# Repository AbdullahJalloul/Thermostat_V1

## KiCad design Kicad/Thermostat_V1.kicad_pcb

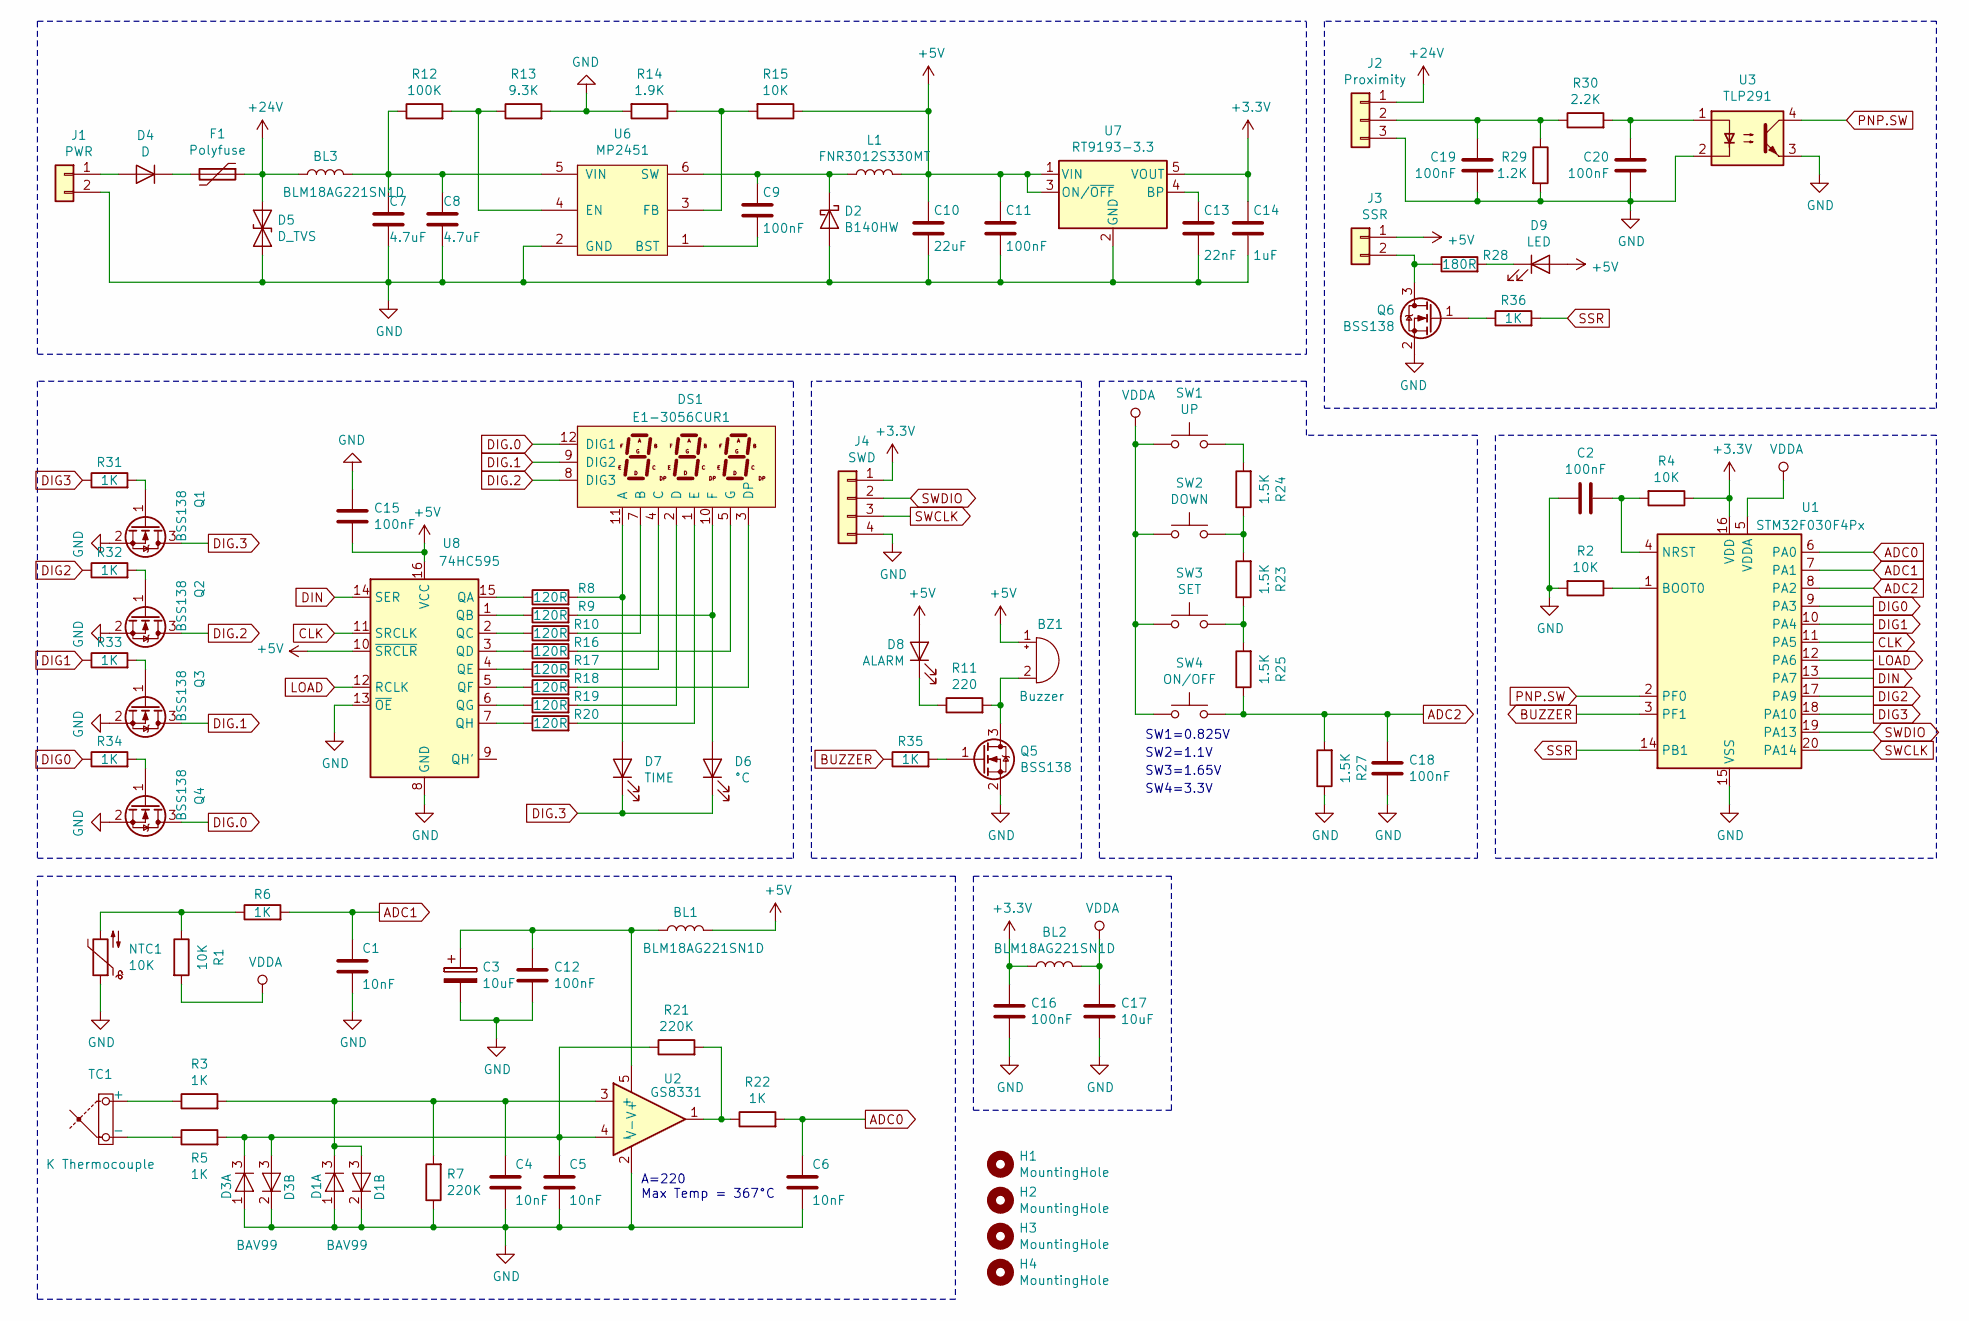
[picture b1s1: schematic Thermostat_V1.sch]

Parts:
BL1, BL2: BLM18AG221SN1D; L_0805
BL3: BLM18AG221SN1D; L_1206
BZ1: Buzzer; Buzzer_12x9.5RM7.6
C1, C4, C5, C6: 10nF; C_0805
C2, C9, C11, C12, C15, C16, C18, C19, C20: 100nF; C_0805
C3: 10uF; CP_Tantalum_Case-A_EIA-3216-18_Reflow
C7, C8: 4.7uF; C_1206
C10: 22uF; C_1206
C13: 22nF; C_0805
C14: 1uF; C_0805
C17: 10uF; C_0805
D1, D3: BAV99; SOT-23
D2: B140HW; D_SOD-123F
D4: D; D_SMA
D5: D_TVS; D_SMA
D6: °C; LED_D5.0mm
D7: TIME; LED_D5.0mm
D8: ALARM; LED_D5.0mm
D9: LED; LED_0805
DS1: E1-3056CUR1; E1-3056-CUR-1-CT
F1: Polyfuse; Fuse_1206_3216Metric
H1, H2, H3, H4: MountingHole; MountingHole_2.5mm
J1: PWR; TerminalBlock_bornier-2_P5.08mm
J2: Proximity; TerminalBlock_bornier-3_P5.08mm
J3: SSR; TerminalBlock_bornier-2_P5.08mm
J4: SWD; Pin_Header_Straight_1x04_Pitch2.54mm
L1: FNR3012S330MT; L_Taiyo-Yuden_MD-3030
NTC1: 10K; R_0805
Q1, Q2, Q3, Q4, Q5, Q6: BSS138; SOT-23
R1, R2, R4, R15: 10K; R_0805
R3, R5, R6, R22, R31, R32, R33, R34, R35, R36: 1K; R_0805
R7, R21: 220K; R_0805
R8, R9, R10, R16, R17, R18, R19, R20: 120R; R_0805
R11: 220; R_0805
R12: 100K; R_0805
R13: 9.3K; R_0805
R14: 1.9K; R_0805
R23, R24, R25, R27: 1.5K; R_0805
R28: 180R; R_0805
R29: 1.2K; R_2512
R30: 2.2K; R_0805
SW1: UP; SW_SPST_PTS645
SW2: DOWN; SW_SPST_PTS645
SW3: SET; SW_SPST_PTS645
SW4: ON/OFF; SW_SPST_PTS645
TC1: K Thermocouple; TerminalBlock_bornier-2_P5.08mm
U1: STM32F030F4Px; TSSOP-20_4.4x6.5mm_Pitch0.65mm
U2: GS8331; SOT-23-5
U3: TLP291; SO-4_4.4x2.3mm_Pitch1.27mm
U6: MP2451; SOT-23-6
U7: RT9193-3.3; SOT-23-5
U8: 74HC595; SOIC-16_3.9x9.9mm_Pitch1.27mm

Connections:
+3V3: BL2.1, C14.2, C16.2, J4.1, R4.1, U1.16 (VDD), U7.5 (VOUT)
+5V: BL1.2, BZ1.1 (-), C10.2, C11.2, C15.1, D8.2 (A), D9.2 (A), J3.1, L1.2, R15.1, U7.1 (VIN), U7.3 (ON/~OFF~), U8.10 (~SRCLR), U8.16 (VCC)
+24V: BL3.1, D5.1 (A1), F1.1, J2.1
ADC0: C6.2, R22.2, U1.6 (PA0)
ADC1: C1.2, R6.2, U1.7 (PA1)
ADC2: C18.2, R25.1, R27.2, SW4.2, U1.8 (PA2)
BUZZER: R35.1, U1.3 (PF1)
CLK: U1.11 (PA5), U8.11 (SRCLK)
DIG0: R34.1, U1.9 (PA3)
DIG1: R33.1, U1.10 (PA4)
DIG2: R32.1, U1.17 (PA9)
DIG3: R31.1, U1.18 (PA10)
DIG.0: DS1.12 (DIG1), Q4.3 (D)
DIG.1: DS1.9 (DIG2), Q3.3 (D)
DIG.2: DS1.8 (DIG3), Q2.3 (D)
DIG.3: D6.1 (K), D7.1 (K), Q1.3 (D)
DIN: U1.13 (PA7), U8.14 (SER)
GND: C1.1, C2.1, C3.2, C4.1, C5.1, C6.1, C7.1, C8.1, C10.1, C11.1, C12.1, C13.1, C14.1, C15.2, C16.1, C17.1, C18.1, C19.1, C20.1, D1.1 (A), D1.2 (K), D2.2 (A), D3.1 (A), D3.2 (K), D5.2 (A2), J1.2, J2.3, J4.4, NTC1.1, Q1.2 (S), Q2.2 (S), Q3.2 (S), Q4.2 (S), Q5.2 (S), Q6.2 (S), R2.2, R7.1, R13.2, R14.2, R27.1, R29.2, U1.15 (VSS), U2.2 (V-), U3.2, U3.3, U6.2 (GND), U7.2 (GND), U8.8 (GND), U8.13 (~OE)
LOAD: U1.12 (PA6), U8.12 (RCLK)
unnamed: BL1.1, C3.1, C12.2, U2.5 (V+)
unnamed: BL3.2, C7.2, C8.2, R12.1, U6.5 (VIN)
unnamed: BZ1.2 (+), Q5.3 (D), R11.2
unnamed: C2.2, R4.2, U1.4 (NRST)
unnamed: C4.2, D1.3 (K), R3.2, R7.2, U2.3 (+)
unnamed: C5.2, D3.3 (K), R5.2, R21.1, U2.4 (-)
unnamed: C9.1, U6.1 (BST)
unnamed: C9.2, D2.1 (K), L1.1, U6.6 (SW)
unnamed: C13.2, U7.4 (BP)
unnamed: C19.2, J2.2, R29.1, R30.1
unnamed: C20.2, R30.2, U3.1
unnamed: D4.1 (K), F1.2
unnamed: D4.2 (A), J1.1
unnamed: D6.2 (A), DS1.10 (F), R9.2
unnamed: D7.2 (A), DS1.11 (A), R8.2
unnamed: D8.1 (K), R11.1
unnamed: D9.1 (K), R28.2
unnamed: DS1.1 (E), R20.2
unnamed: DS1.2 (D), R19.2
unnamed: DS1.3 (DP), R18.2
unnamed: DS1.4 (C), R17.2
unnamed: DS1.5 (G), R16.2
unnamed: DS1.7 (B), R10.2
unnamed: J3.2, Q6.3 (D), R28.1
unnamed: NTC1.2, R1.1, R6.1
unnamed: Q1.1 (G), R31.2
unnamed: Q2.1 (G), R32.2
unnamed: Q3.1 (G), R33.2
unnamed: Q4.1 (G), R34.2
unnamed: Q5.1 (G), R35.2
unnamed: Q6.1 (G), R36.1
unnamed: R2.1, U1.1 (BOOT0)
unnamed: R3.1, TC1.1 (+)
unnamed: R5.1, TC1.2 (-)
unnamed: R8.1, U8.15 (QA)
unnamed: R9.1, U8.1 (QB)
unnamed: R10.1, U8.2 (QC)
unnamed: R12.2, R13.1, U6.4 (EN)
unnamed: R14.1, R15.2, U6.3 (FB)
unnamed: R16.1, U8.3 (QD)
unnamed: R17.1, U8.4 (QE)
unnamed: R18.1, U8.5 (QF)
unnamed: R19.1, U8.6 (QG)
unnamed: R20.1, U8.7 (QH)
unnamed: R21.2, R22.1, U2.1
unnamed: R23.1, R25.2, SW3.2
unnamed: R23.2, R24.1, SW2.2
unnamed: R24.2, SW1.2
PNP.SW: U1.2 (PF0), U3.4
SSR: R36.2, U1.14 (PB1)
SWCLK: J4.3, U1.20 (PA14)
SWDIO: J4.2, U1.19 (PA13)
VDDA: BL2.2, C17.2, R1.2, SW1.1, SW2.1, SW3.1, SW4.1, U1.5 (VDDA)

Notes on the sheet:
SW1=0.825V
SW2=1.1V
SW3=1.65V
SW4=3.3V
A=220 Max Temp = 367°C

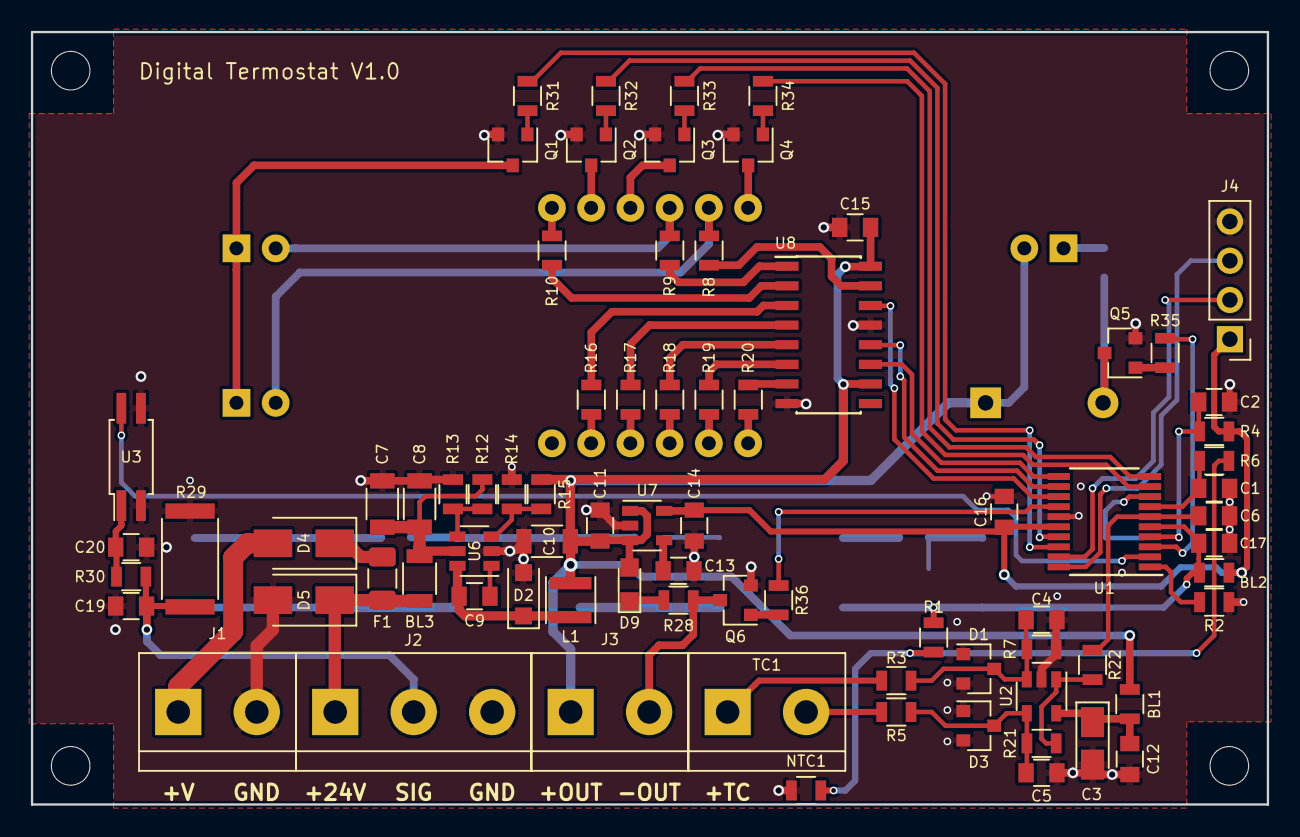
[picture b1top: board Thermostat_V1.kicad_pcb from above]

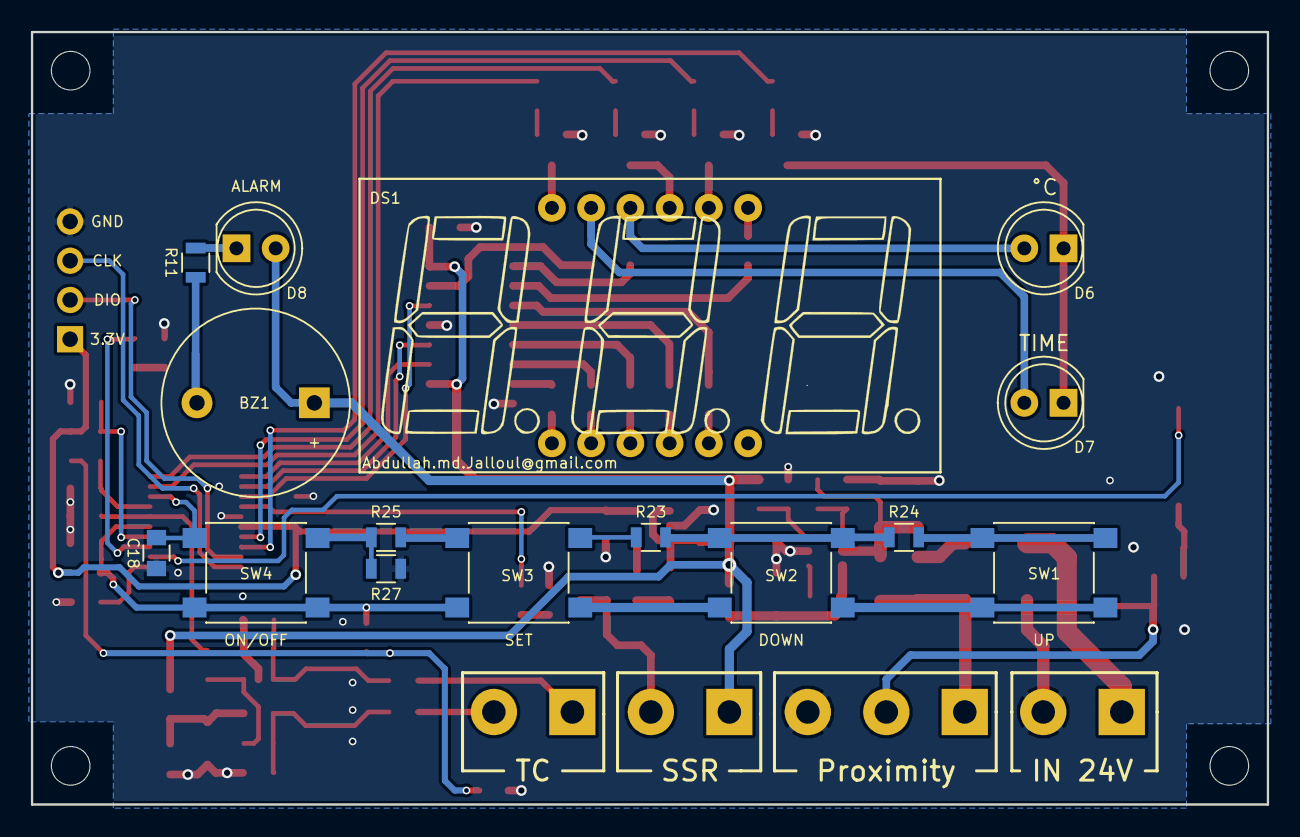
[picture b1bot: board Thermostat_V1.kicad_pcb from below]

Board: 2 copper layers, 80.0 x 50.0 mm, 97 parts (15 on the bottom side), 72 nets.

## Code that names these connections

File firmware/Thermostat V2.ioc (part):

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Mcu.Name=STM32F030F4Px
Mcu.Package=TSSOP20
Mcu.UserName=STM32F030F4Px
PA0.Mode=IN0
PA0.Signal=ADC_IN0
PA1.Mode=IN1
PA1.Signal=ADC_IN1
PA10.GPIOParameters=GPIO_Label
PA10.GPIO_Label=DIG3
PA10.Signal=GPIO_Output
PA13.Mode=Serial_Wire
PA13.Signal=SYS_SWDIO
PA14.Mode=Serial_Wire
PA14.Signal=SYS_SWCLK
PA2.Mode=IN2
PA2.Signal=ADC_IN2
PA3.GPIOParameters=GPIO_Label
PA3.GPIO_Label=DIG0
PA3.Signal=GPIO_Output
PA4.GPIOParameters=GPIO_Label
PA4.GPIO_Label=DIG1
PA4.Signal=GPIO_Output
PA5.GPIOParameters=GPIO_Label
PA5.GPIO_Label=SCK
PA5.Mode=Simplex_Bidirectional_Master
PA5.Signal=SPI1_SCK
PA6.GPIOParameters=GPIO_Label
PA6.GPIO_Label=LATCH
PA6.Signal=GPIO_Output
PA7.GPIOParameters=GPIO_Label
PA7.GPIO_Label=DATA
PA7.Mode=Simplex_Bidirectional_Master
PA7.Signal=SPI1_MOSI
PA9.GPIOParameters=GPIO_Label
PA9.GPIO_Label=DIG2
PA9.Signal=GPIO_Output
PB1.Signal=S_TIM14_CH1
PF0-OSC_IN.GPIOParameters=GPIO_PuPd,GPIO_Label
PF0-OSC_IN.GPIO_Label=PNP_SW
PF0-OSC_IN.GPIO_PuPd=GPIO_PULLUP
PF0-OSC_IN.Signal=GPIO_Input
PF1-OSC_OUT.GPIOParameters=GPIO_Label
PF1-OSC_OUT.GPIO_Label=BUZZER
PF1-OSC_OUT.Signal=GPIO_Output
RCC.SYSCLKFreq_VALUE=16000000
RCC.SYSCLKSource=RCC_SYSCLKSOURCE_PLLCLK
board=custom

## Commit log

2019-05-15 Revert "Initial commit"
    This reverts commit 4860c0b61b0ce844791a99ae376173cfcdf9798c.
2019-05-15 modifying
